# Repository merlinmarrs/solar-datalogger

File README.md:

# solar-datalogger
A solar powered datalogger that can interface with I2C and SPI sensors

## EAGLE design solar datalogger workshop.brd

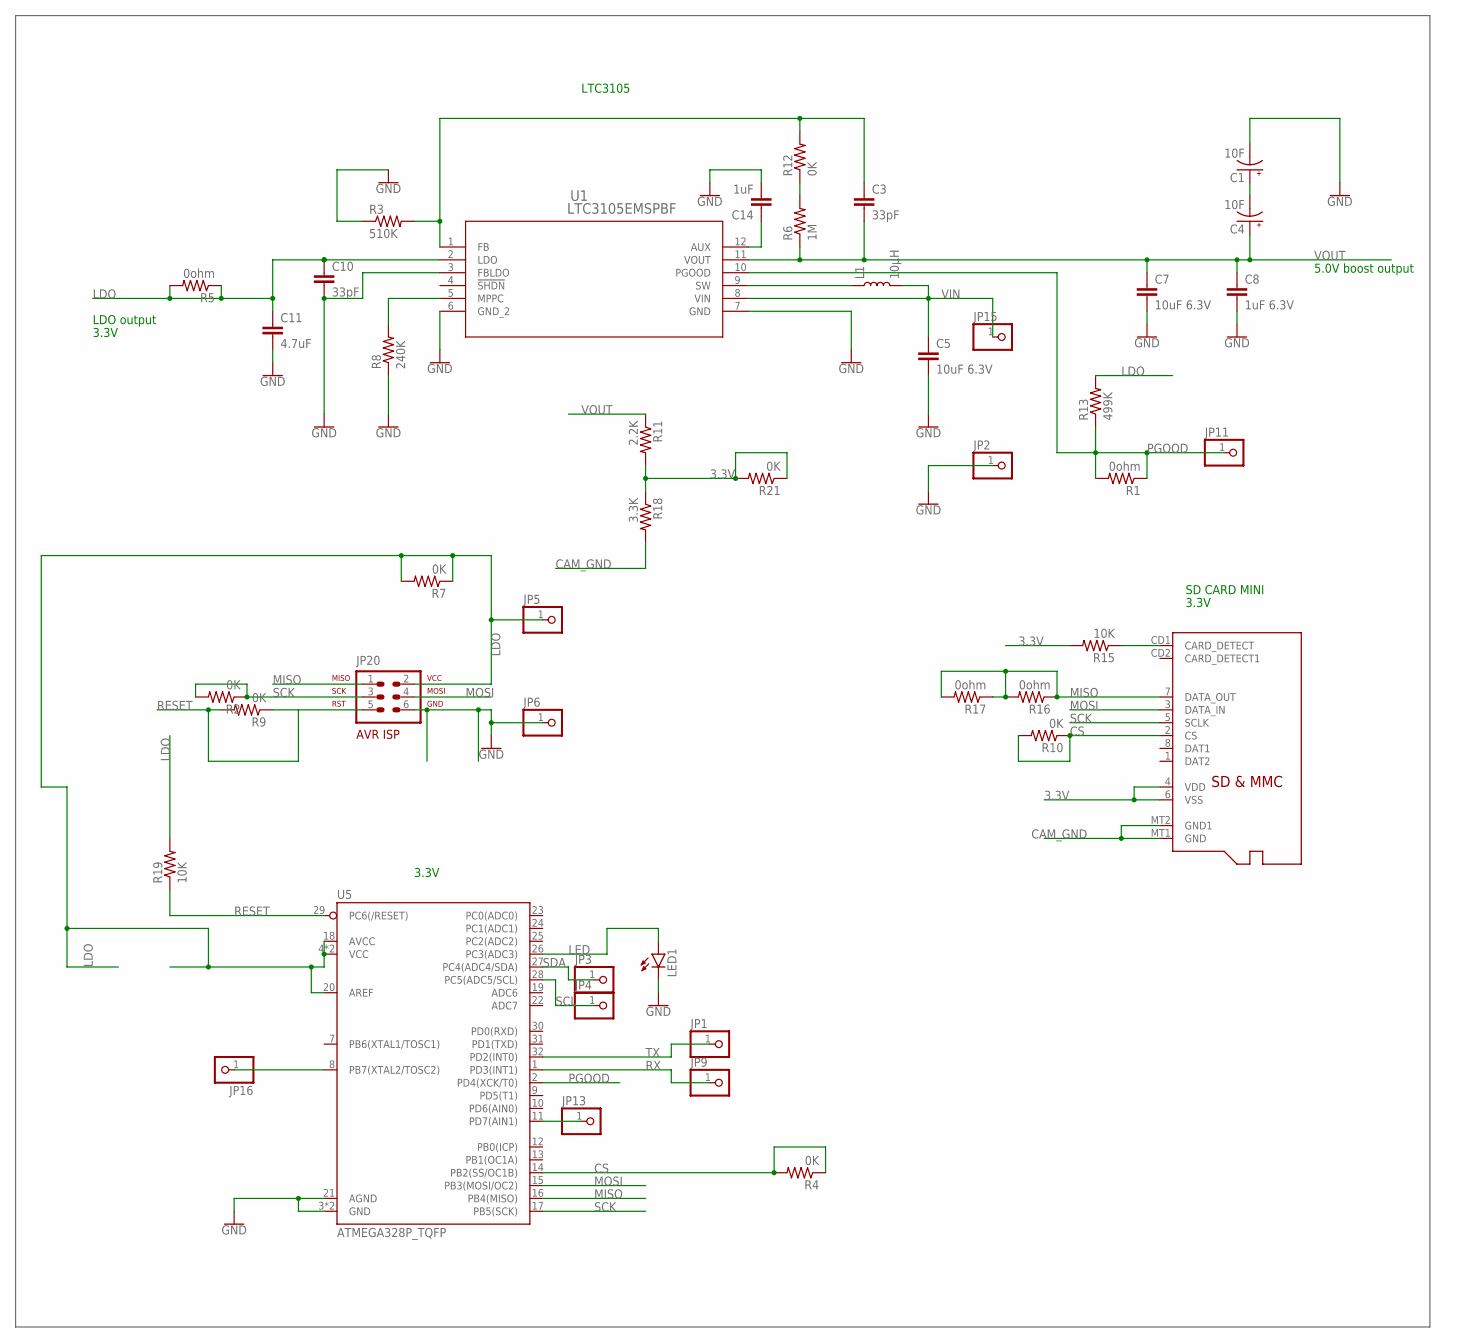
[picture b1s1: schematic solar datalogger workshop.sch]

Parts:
C1, C4: 10F; CAP-RADIAL-5MM-21.5MM
C3, C10: 33pF; 1206
C5, C7: 10uF 6.3V; 1206
C8: 1uF 6.3V; 1206
C11: 4.7uF; 1206
C14: 1uF; 1206
JP1, JP2, JP3, JP4, JP5, JP6, JP9, JP11, JP13, JP15, JP16: PINHD-1X1CB; 1X01-CLEANBIG
JP20: AVR-ISP-6HORZ; AVR-ISP-6R
L1: 10µH; INDUCTOR_2.2UH
LED1: LEDSML1206; SML1206
R1, R5, R16, R17: 0ohm; R1206
R2, R4, R7, R9, R10, R12, R21: 0K; R1206
R3: 510K; R1206
R6: 1M; R1206
R8: 240K; R1206
R11: 2.2K; R1206
R13: 499K; R1206
R15, R19: 10K; R1206
R18: 3.3K; R1206
U1: LTC3105EMSPBF; MSOP-12_MS
U5: ATMEGA328P_TQFP; TQFP32-08
U$1: MICROSD

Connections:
3.3V: R11.2, R15.2, R18.1, R21.1, R21.2, U$1.4 (VDD), U$1.6 (VSS)
CAM_GND: R18.2, U$1.MT1 (GND), U$1.MT2 (GND1)
CS: R4.1, R4.2, R10.1, R10.2, U5.14 (PB2(SS/OC1B)), U$1.2 (CS)
GND: C1.-, C5.2, C7.2, C8.2, C10.2, C11.2, C14.2, JP2.1, JP6.1, JP20.6, LED1.C, R3.1, R8.1, U1.3 (FBLDO), U1.6 (GND_2), U1.7 (GND), U5.3 (GND), U5.5 (GND), U5.21 (AGND)
LDO: C10.1, C11.1, JP5.1, JP20.2, R5.1, R5.2, R7.1, R7.2, R13.2, R19.2, U1.2 (LDO), U5.4 (VCC), U5.6 (VCC), U5.18 (AVCC), U5.20 (AREF)
LED: LED1.A, U5.26 (PC3(ADC3))
MISO: JP20.1, R16.1, R16.2, R17.1, R17.2, U5.16 (PB4(MISO)), U$1.7 (DATA_OUT)
MOSI: JP20.4, U5.15 (PB3(MOSI/OC2)), U$1.3 (DATA_IN)
unnamed: C3.1, R3.2, R12.2, U1.1 (FB)
unnamed: C1.+, C4.-
unnamed: L1.P$1 (1), U1.9 (SW)
unnamed: C14.1, U1.12 (AUX)
unnamed: R8.2, U1.5 (MPPC)
unnamed: R6.2, R12.1
unnamed: JP13.1, U5.11 (PD7(AIN1))
unnamed: JP16.1, U5.8 (PB7(XTAL2/TOSC2))
unnamed: R15.1, U$1.CD1 (CARD_DETECT)
PGOOD: JP11.1, R1.1, R1.2, R13.1, U1.10 (PGOOD), U5.2 (PD4(XCK/T0))
RESET: JP20.5, R9.1, R9.2, R19.1, U5.29 (PC6(/RESET))
RX: JP9.1, U5.1 (PD3(INT1))
SCK: JP20.3, R2.1, R2.2, U5.17 (PB5(SCK)), U$1.5 (SCLK)
SCL: JP4.1, U5.28 (PC5(ADC5/SCL))
SDA: JP3.1, U5.27 (PC4(ADC4/SDA))
TX: JP1.1, U5.32 (PD2(INT0))
VIN: C5.1, JP15.1, L1.P$2 (2), U1.8 (VIN)
VOUT: C3.2, C4.+, C7.1, C8.1, R6.1, R11.1, U1.11 (VOUT)

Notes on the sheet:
5.0V boost output
LDO output
3.3V
LTC3105
SD CARD MINI

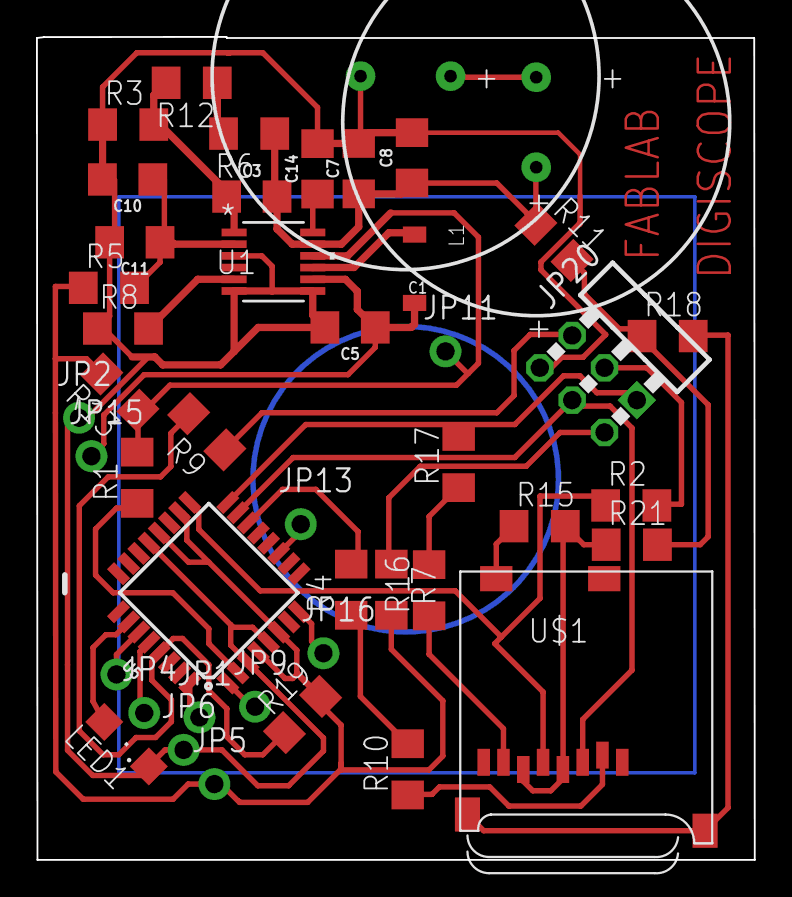
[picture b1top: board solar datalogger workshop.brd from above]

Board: 2 copper layers, 39.9 x 45.7 mm, 45 parts (1 on the bottom side), 26 nets.

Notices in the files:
parts and their libraries:
SparkFun-Coils: Licensing: Creative Commons ShareAlike 4.0 International - https://creativecommons.org/licenses/by-sa/4.0
